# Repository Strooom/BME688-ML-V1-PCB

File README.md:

# BME688 Machine Learning PCB

KiCAD design files for the BME688 Machine Learning PCB.

## Front render

## Back render

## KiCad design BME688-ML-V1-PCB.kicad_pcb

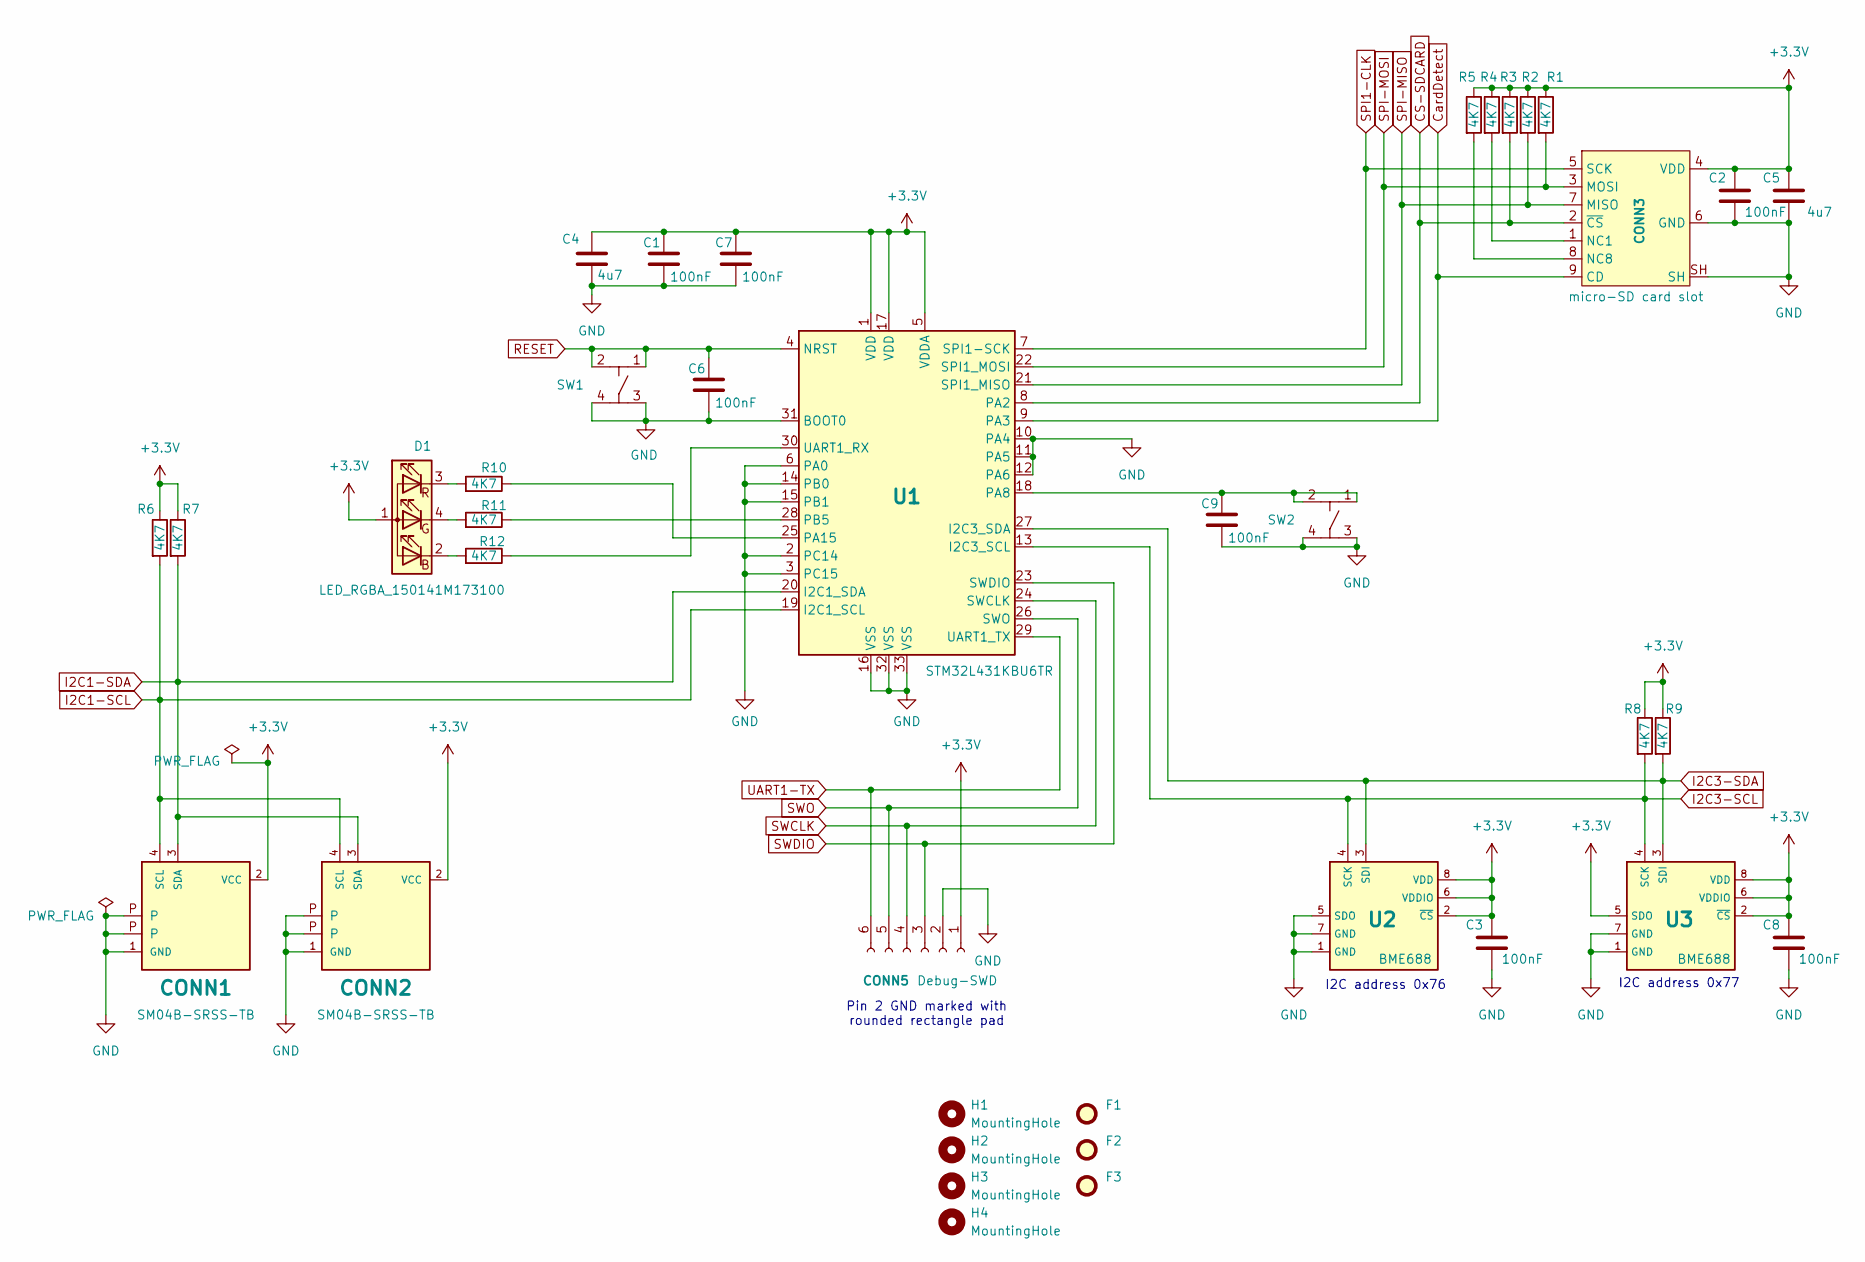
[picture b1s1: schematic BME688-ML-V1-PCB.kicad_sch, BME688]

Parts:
C1, C2, C3, C6, C7, C8, C9: KGM15AR71C104KT; C_0603_nominal; manufacturerPartNumber KGM15AR71C104KT; digikeyPartNumber 478-KGM15AR71C104KTCT-ND
C4, C5: C0603C475K8PAC7411; C_0603_nominal; manufacturerPartNumber C0603C475K8PAC7411; digikeyPartNumber 399-C0603C475K8PAC7411CT-ND
CONN1, CONN2: SM04B-SRSS-TB; JST_SH_SM04B-SRSS-TB_1x04-1MP_P1.00mm_Horizontal; mouserPartNumber 306-SM04BSRSSTBLFDNP
CONN3: MSD-1-A; mouserPartNumber 179-MSD-1-A
CONN5: notApplicable; DebugConnector_1x06_P2.54mm; manufacturerPartNumber notApplicable; digikeyPartNumber notApplicable
D1: LED_RGBA_150141M173100; RGB_LED_150141M173100
F1, F2, F3: Fiducial; Fiducial_0.5mm_Mask1mm; manufacturerPartNumber notApplicable; digikeyPartNumber notApplicable
H1, H2, H3, H4: MountingHole; MountingHole_2.2mm_M2; manufacturerPartNumber notApplicable; digikeyPartNumber notApplicable
R1, R2, R3, R4, R5, R6, R7, R8, R9, R10, R11, R12: CR0603-FX-4701ELF; R_0603_nominal; manufacturerPartNumber CR0603-FX-4701ELF; mouserPartNumber 652-CR0603FX-4701ELF
SW1, SW2: 434133025816; Wurth-434133025816; manufacturerPartNumber 434133025816; digikeyPartNumber 732-13663-1-ND
U1: STM32L431KBU6TR; QFN-32-1EP_5x5mm_P0.5mm_EP3.45x3.45mm; manufacturerPartNumber STM32L431KBU6TR; digikeyPartNumber 497-18831-1-ND
U2, U3: BME688; manufacturerPartNumber BME688; digikeyPartNumber 828-BME688CT-ND

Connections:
+3.3V: C1.1, C2.1, C3.1, C4.1, C5.1, C7.1, C8.1, CONN1.2 (VCC), CONN2.2 (VCC), CONN3.4 (VDD), CONN5.1, D1.1 (A), R1.1, R2.1, R3.1, R4.1, R5.1, R6.1, R7.1, R8.1, R9.1, U1.1 (VDD), U1.5 (VDDA), U1.17 (VDD), U2.2 (~CS), U2.6 (VDDIO), U2.8 (VDD), U3.2 (~CS), U3.5 (SDO), U3.6 (VDDIO), U3.8 (VDD)
CS-SDCARD: CONN3.2 (~CS), R3.2, U1.8 (PA2)
CardDetect: CONN3.9 (CD), U1.9 (PA3)
GND: C1.2, C2.2, C3.2, C4.2, C5.2, C6.2, C7.2, C8.2, C9.2, CONN1.1 (GND), CONN1.P, CONN2.1 (GND), CONN2.P, CONN3.6 (GND), CONN3.SH, CONN5.2, SW1.3, SW1.4, SW2.3, SW2.4, U1.2 (PC14), U1.3 (PC15), U1.6 (PA0), U1.10 (PA4), U1.11 (PA5), U1.12 (PA6), U1.14 (PB0), U1.15 (PB1), U1.16 (VSS), U1.31 (BOOT0), U1.32 (VSS), U1.33 (VSS), U2.1 (GND), U2.5 (SDO), U2.7 (GND), U3.1 (GND), U3.7 (GND)
I2C1-SCL: CONN1.4 (SCL), CONN2.4 (SCL), R6.2, U1.19 (I2C1_SCL)
I2C1-SDA: CONN1.3 (SDA), CONN2.3 (SDA), R7.2, U1.20 (I2C1_SDA)
I2C3-SCL: R8.2, U1.13 (I2C3_SCL), U2.4 (SCK), U3.4 (SCK)
I2C3-SDA: R9.2, U1.27 (I2C3_SDA), U2.3 (SDI), U3.3 (SDI)
unnamed: CONN3.1 (NC1), R4.2
unnamed: CONN3.8 (NC8), R5.2
unnamed: D1.2 (BK), R12.2
unnamed: D1.4 (GK), R11.2
unnamed: D1.3 (RK), R10.2
unnamed: C9.1, SW2.1, SW2.2, U1.18 (PA8)
unnamed: R10.1, U1.25 (PA15)
unnamed: R11.1, U1.28 (PB5)
unnamed: R12.1, U1.30 (UART1_RX)
RESET: C6.1, SW1.1, SW1.2, U1.4 (NRST)
SPI1-CLK: CONN3.5 (SCK), U1.7 (SPI1-SCK)
SPI-MISO: CONN3.7 (MISO), R2.2, U1.21 (SPI1_MISO)
SPI-MOSI: CONN3.3 (MOSI), R1.2, U1.22 (SPI1_MOSI)
SWCLK: CONN5.4, U1.24 (SWCLK)
SWDIO: CONN5.3, U1.23 (SWDIO)
SWO: CONN5.5, U1.26 (SWO)
UART1-TX: CONN5.6, U1.29 (UART1_TX)

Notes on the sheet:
Pin 2 GND marked with rounded rectangle pad
I2C address 0x76
I2C address 0x77

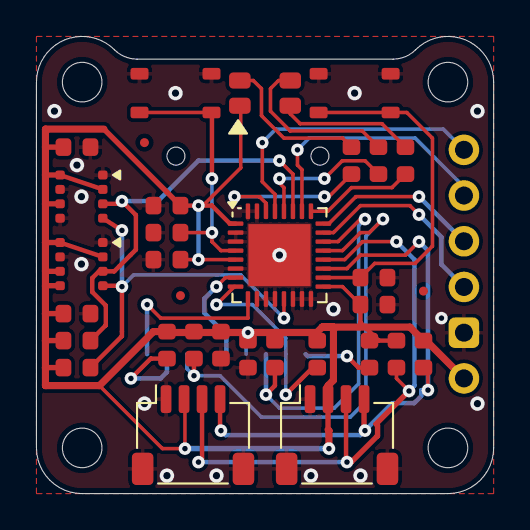
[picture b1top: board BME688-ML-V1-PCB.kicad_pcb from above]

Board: 2 copper layers, 25.4 x 25.4 mm, 38 parts (1 on the bottom side), 25 nets.

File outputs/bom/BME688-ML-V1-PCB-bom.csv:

Row,Description,Part,References,Value,Footprint,Quantity Per PCB,Status,Datasheet,GPN,manufacturerName,manufacturerPartNumber,digikeyPartNumber,mouserPartNumber,octopartUrl,MPN,manufacturer,supplier1Name,supplier1PartNumber,supplier1PartURL,supplier2Name,supplier2PartNumber,supplier2PartURL,remark
1,4u7,C,C4 C5,C0603C475K8PAC7411,C_0603_nominal,2, ,https://www.mouser.be/datasheet/2/447/KEM_C1006_X5R_SMD-3316465.pdf,GPC0603475,Yageo - Kemet,C0603C475K8PAC7411,399-C0603C475K8PAC7411CT-ND,80-C0603C475K8PACLR,https://octopart.com/c0603c475k8pac7411-kemet-75146718?r=,C0603C475K8PAC7411,,,,,,,,
2,100nF,C,C1 C2 C3 C6 C7 C8,KGM15AR71C104KT,C_0603_nominal,6, ,https://www.mouser.be/datasheet/2/40/KGM_X7R-3223212.pdf,GPC0603104,KYOCERA AVX,KGM15AR71C104KT,478-KGM15AR71C104KTCT-ND,581-KGM15AR71C104KT,https://octopart.com/kgm15ar71c104kt-avx-136559929?r=sp,KGM15AR71C104KT,,,,,,,,
3,micro-SD card slot,microSdCard,CONN3,MSD-1-A,MSD-1-A,1, ,https://www.mouser.be/datasheet/2/670/msd_1_a-3367597.pdf,,CUI Devices,MSD-1-A,,179-MSD-1-A,https://octopart.com/msd-1-a-same+sky-145369555?r=sp,MSD-1-A,,,,,,,,
4,Qwiic,Qwiic connector,CONN1 CONN2,SM04B-SRSS-TB,JST_SH_SM04B-SRSS-TB_1x04-1MP_P1.00mm_Horizontal,2, ,https://www.mouser.be/datasheet/2/813/eSH-2487316.pdf,,Sparkfun - JST,SM04B-SRSS-TB(LF)(DN)(P),,306-SM04BSRSSTBLFDNP,https://octopart.com/sm04b-srss-tb%28lf%29%28dn%29%28p%29-js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,SM04B-SRSS-TB,,,,,,,,
5,Debug-SWD,Conn_01x06_Socket,CONN5,notApplicable,DebugConnector_1x06_P2.54mm,1, ,notApplicable,,notApplicable,notApplicable,notApplicable,notApplicable,notApplicable,,,,,,,,,
6,4K7,R,R1 R2 R3 R4 R5 R6 R7 R8 R9,CR0603-FX-4701ELF,R_0603_nominal,9, ,https://www.mouser.be/datasheet/2/54/cr-1858361.pdf,GPR06034K7,Bourns,CR0603-FX-4701ELF,CR0603-FX-4701ELFCT-ND,652-CR0603FX-4701ELF,https://octopart.com/cr0603-fx-4701elf-bourns-3867100?r=sp,CR0603-FX-4701ELF,,,,,,,,
7,Application buttonswitch,Switch_434133025816,SW1,434133025816,Wurth-434133025816,1, ,https://www.we-online.com/components/products/datasheet/4341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,,Wurth Electronics,434133025816,732-13663-1-ND,710-434133025816,https://octopart.com/434133025816-wurth+elektronik-99472342?r=sp,434133025816,,,,,,,,
8,"Air Quality Sensors MEMS gas, humidity, pressure and temperature sensor",BME688,U2 U3,BME688,BME688,2, ,https://ae-bst.resource.bosch.com/media/_tech/media/datashee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,,Bosch Sensortec,BME688,828-BME688CT-ND,262-BME688,https://octopart.com/bme688-bosch+tools-116090840?r=sp,BME688,Bosch Sensortec,Mouser,262-BME680,https://www.mouser.be/ProductDetail/Bosch-Sensortec/BME680?q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,Digi-Key,828-1077-1-ND,https://www.digikey.be/nl/products/detail/bosch-sensortec/BM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,
9,"STMicroelectronics Arm Cortex-M4 MCU, 128-256KB flash, 64KB RAM, 80 MHz, 1.71-3.6V, 26 GPIO, UFQFPN32",STM32L431K,U1,STM32L431KBU6TR,QFN-32-1EP_5x5mm_P0.5mm_EP3.45x3.45mm,1, ,https://www.st.com/resource/en/datasheet/stm32l431kb.pdf,,ST,STM32L431KBU6TR,497-18831-1-ND,511-STM32L431KBU6TR,https://octopart.com/stm32l431kbu6tr-stmicroelectronics-8920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,STM32L431KBU6TR,,,,,,,,





Project info:
Schematic:,BME688-ML-V1-PCB
Variant:,default
Revision:,V1
Date:,2024-09-18
KiCad Version:,8.0.6+1
Statistics:
Component Groups:,9
Component Count:,25
Fitted Components:,25
Number of PCBs:,1
Total Components:,25

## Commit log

2024-09-27 add workflow
2024-09-27 remove backups from repo
2024-09-28 extend to exclude .lck files
2024-09-28 reorganize folders
2024-09-28 remove dependency on global library
2024-09-28 fix 3dmodel for R0603 and C0603
2024-09-28 commit CI artifacts to repository io attaching them to the workflow
2024-09-28 fix permissions for action bot
2024-09-28 Continuous Integration Build Artifacts
2024-09-28 exp001 try to add renders to repo and commit
2024-09-28 remove dependencies on global library
2024-09-29 add git add to add workflow generated files to the repository
2024-09-29 add qwiic 3d model
2024-09-29 fix both QWIIC connectors
2024-09-29 adjusting blender options
2024-09-29 trying to export 2 render types
2024-09-29 one more export format
2024-09-29 fix filename error
2024-09-29 remove pcb_print
2024-09-29 fix folders
2024-09-29 remove folder
2024-09-29 test
2024-09-29 test002
2024-09-29 test003
2024-09-30 fix
    Tie BOOT0/PH3 to GND, as without the SW is not running stable..
2024-09-30 modified output directory for erc and drc
2024-09-30 style
    quote around reports directory name
2024-09-30 cleanup old files
2024-09-30 cleanup workflow.yaml
2024-10-03 more output formats
2024-10-03 fix output options add new pin assignment for V1.2
2024-10-03 take options from example
2024-10-03 rename file and improve kibot yaml
2024-10-03 rename
2024-10-03 add workflow generated files
2024-10-04 Redesign for V1.2
    Moved BME688 onto its own I2C bus.
    Placed 2 BME688
2024-10-04 Add CC logo
2024-10-04 improving workflow
2024-10-04 fix draw_stackup
2024-10-04 remove board stackup
2024-10-04 fix pcb_print
2024-10-04 remove old files improve scaling of pcb pdf
2024-10-04 finetuning
2024-10-04 experimenting with solder mask color
2024-10-04 remove failing output
2024-10-04 small improvements in signal routing
2024-10-04 extend workflow with versioning
    create next version info
2024-10-04 removed buildfilename
2024-10-04 add generation of version.yaml file
2024-10-04 correct syntax of generated yaml file
2024-10-04 reorganize workflow files name and path
2024-10-04 fix path for import yaml file
2024-10-04 move and add GND stitching vias
2024-10-04 improve colors for pcb_print
2024-10-04 add readme.md
2024-10-04 fix workflow badge
2024-10-04 experiment with point_of_view for blender
2024-10-04 test with 2 renders
2024-10-04 fix csv bom
2024-10-05 improve
    1. remove .csv from .gitignore so KiBOT can generate and add a csv.bom
    2. change view on render
2024-10-05 ocb_print color experiments
2024-10-05 Add back image to readme.md
2024-10-05 fix pcb_print color code
2024-10-05 fillet tracks for more beauty
2024-12-21 updating BOM
2024-12-24 Add #3 and fix #5
    Add application button
    Add RGB led
    Move SD-card connector to align inserted card with PCB edge
2024-12-24 Fix overlapping courtyard
